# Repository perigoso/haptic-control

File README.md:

# haptic-control

PCB designed for (Someone else's) masters degree final project in eletrical-engineering

Made in the context of a research internship at IPL (Polytechnic Institute of Leiria)

## Authors

- Rafael Silva
- João Silva

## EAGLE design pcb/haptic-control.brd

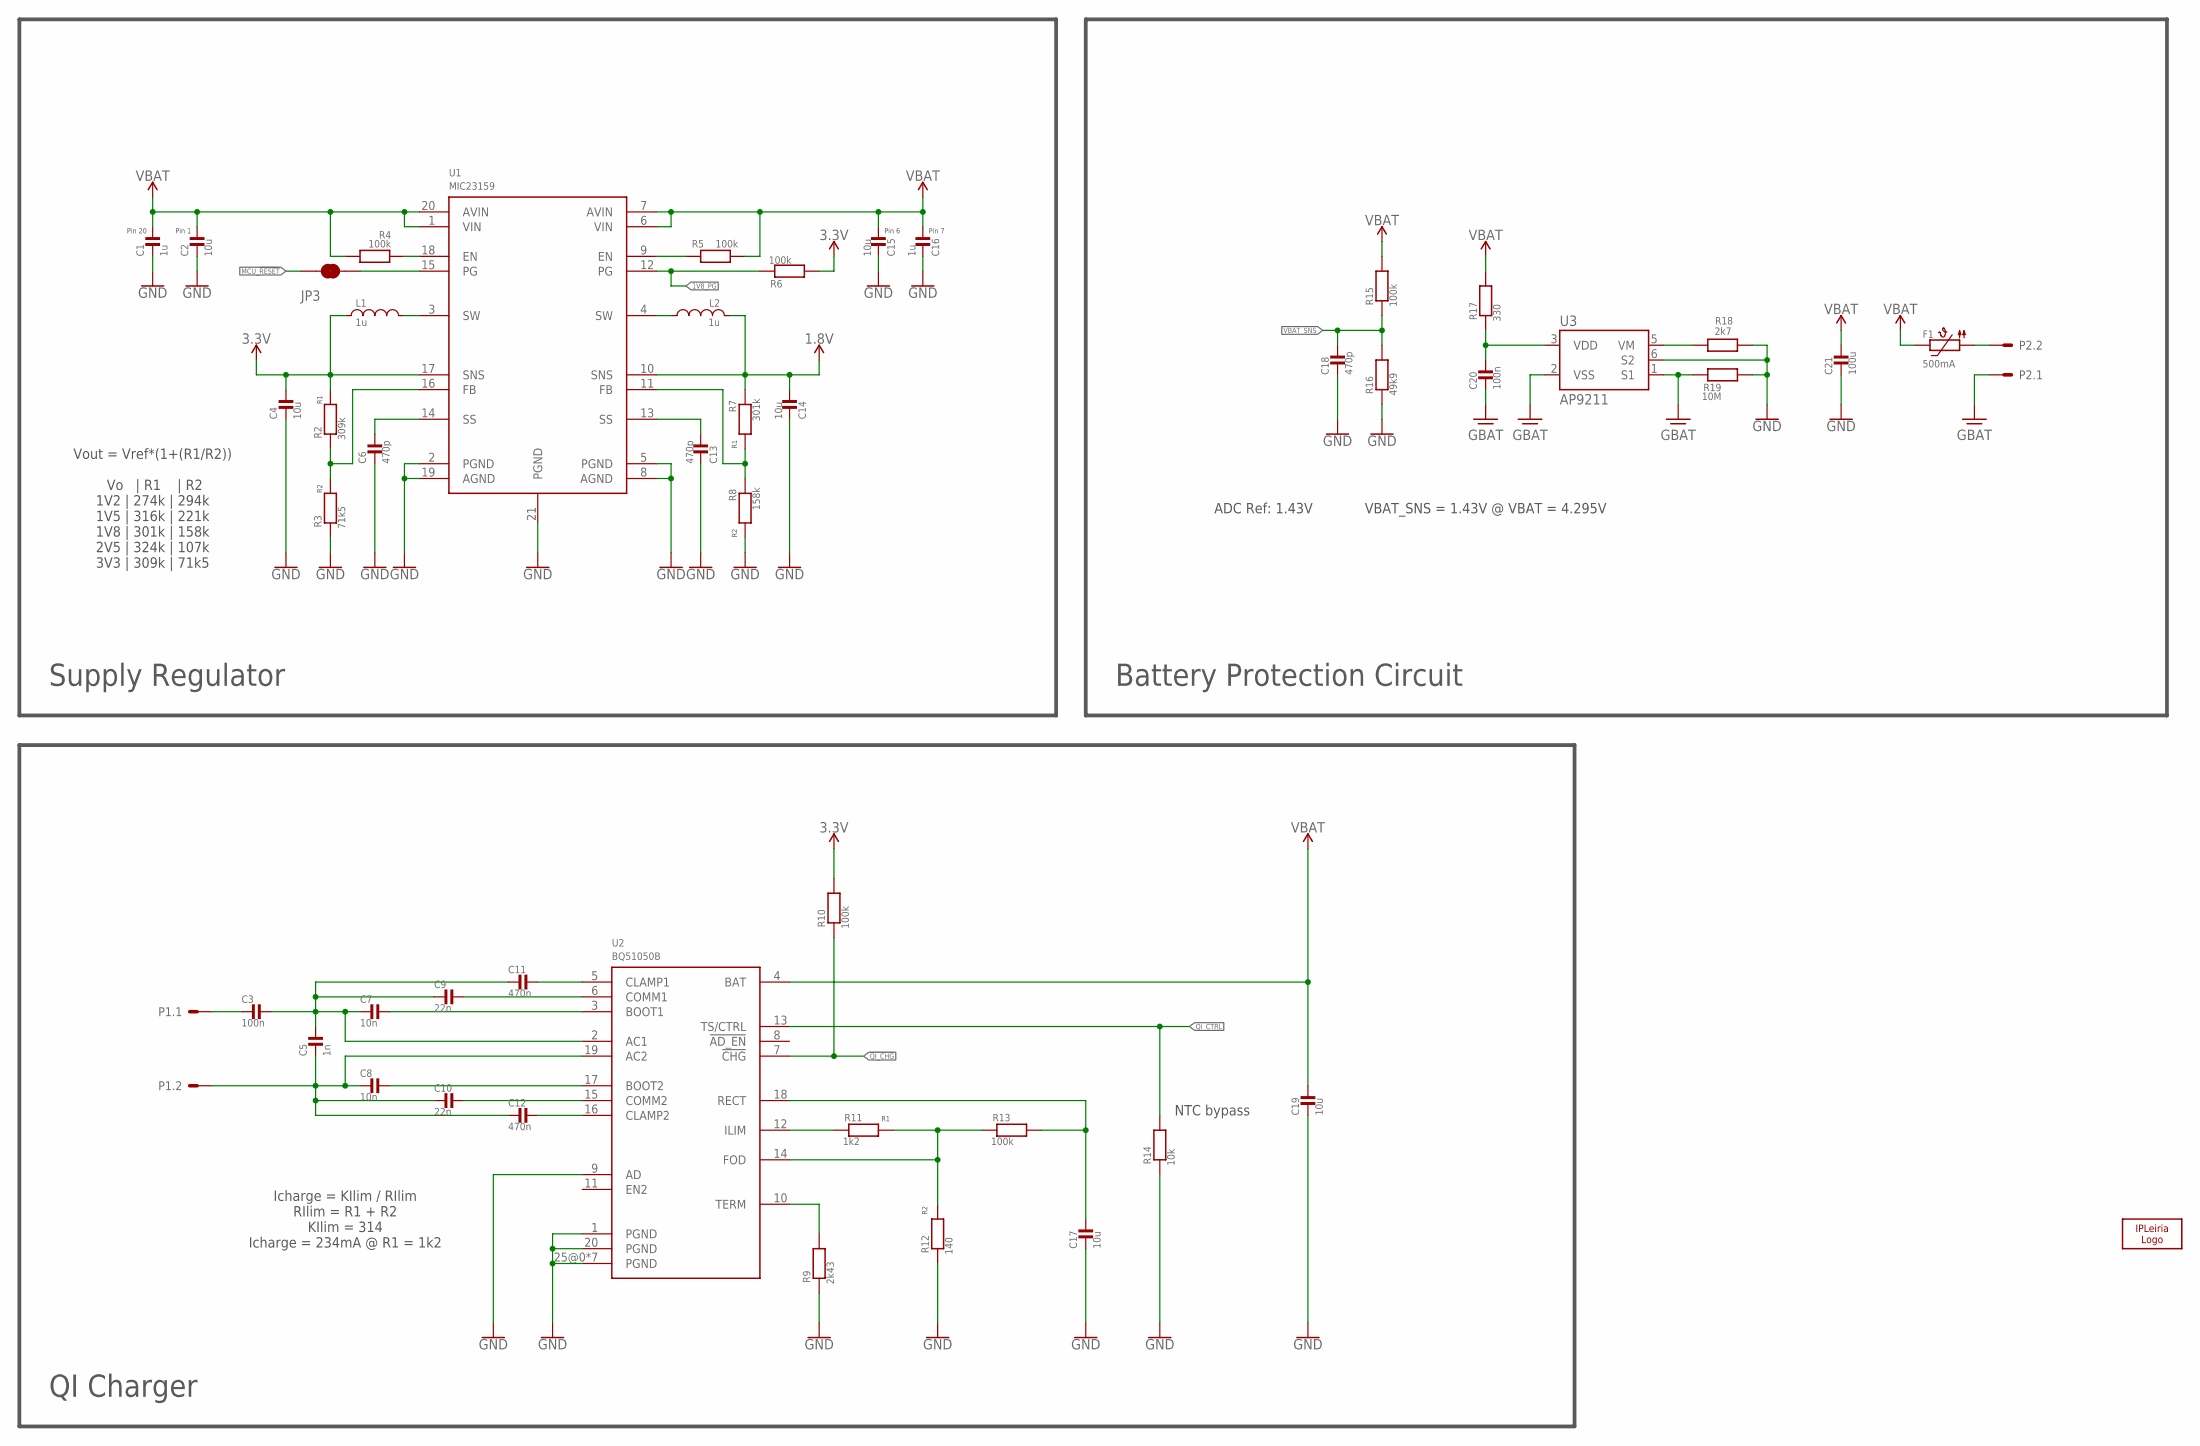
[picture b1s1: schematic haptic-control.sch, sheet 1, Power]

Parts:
C1, C16: 1u; 0603_WAVE
C2, C4, C14, C15, C17, C19: 10u; 0603_WAVE
C3, C20: 100n; _0402
C5: 1n; _0402
C6, C13, C18: 470p; _0402
C7, C8: 10n; _0402
C9, C10: 22n; _0402
C11, C12: 470n; _0402
C21: 100u; _1206
F1: 500mA; 0805
JP3: JUMPER-SMT_2_NC_TRACE_SILK; SMT-JUMPER_2_NC_TRACE_SILK
L1, L2: 1u; _0806
LOGO1: IPL-10MM; IPL_10MM
P1, P2: 2P-PAD_1X3.5; PAD1X3_5MM-2P
R2: 309k; _0402
R3: 71k5; _0402
R4, R5, R6, R10, R13, R15: 100k; _0402
R7: 301k; _0402
R8: 158k; _0402
R9: 2k43; _0402
R11: 1k2; _0402
R12: 140; _0402
R14: 10k; _0402
R16: 49k9; _0402
R17: 330; _0402
R18: 2k7; _0402
R19: 10M; _0402
U1: MIC23159; VQFN20
U2: BQ51050B; VQFN20
U3: AP9211; DFN2030-6

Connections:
1.8V: C14.P$1, L2.1, R7.1, U1.10 (SNS); also elsewhere on the board
1V8_PG: R6.1, U1.12 (PG); also elsewhere on the board
3.3V: C4.P$1, L1.1, R2.2, R6.2, R10.2, U1.17 (SNS); also elsewhere on the board
!QI_CHG: R10.1, U2.7 (!CHG); also elsewhere on the board
GBAT: C20.2, P2.1, R19.1, U3.1 (S1), U3.2 (VSS)
GND: C1.P$2, C2.P$2, C4.P$2, C6.2, C13.2, C14.P$2, C15.P$2, C16.P$2, C17.P$2, C18.2, C19.P$2, C21.2, R3.1, R8.2, R9.1, R12.1, R14.1, R16.1, R18.1, R19.2, U1.2 (PGND), U1.5 (PGND), U1.8 (AGND), U1.19 (AGND), U1.21 (PGND), U2.1 (PGND), U2.9 (AD), U2.20 (PGND), U2.25@0 (PGND), U2.25@1 (PGND), U2.25@2 (PGND), U2.25@3 (PGND), U2.25@4 (PGND), U2.25@5 (PGND), U2.25@6 (PGND), U3.6 (S2); also elsewhere on the board
MCU_!RESET: JP3.1; also elsewhere on the board
MPU_PWR: R5.1, U1.9 (EN)
unnamed: R18.2, U3.5 (VM)
unnamed: F1.1, P2.2
unnamed: C20.1, R17.1, U3.3 (VDD)
unnamed: R2.1, R3.2, U1.16 (FB)
unnamed: R4.1, U1.18 (EN)
unnamed: L1.2, U1.3 (SW)
unnamed: C6.1, U1.14 (SS)
unnamed: L2.2, U1.4 (SW)
unnamed: C13.1, U1.13 (SS)
unnamed: R7.2, R8.1, U1.11 (FB)
unnamed: R11.2, R12.2, R13.1, U2.14 (FOD)
unnamed: R11.1, U2.12 (ILIM)
unnamed: C17.P$1, R13.2, U2.18 (RECT)
unnamed: R9.2, U2.10 (TERM)
unnamed: C11.1, U2.5 (CLAMP1)
unnamed: C9.1, U2.6 (COMM1)
unnamed: C7.1, U2.3 (BOOT1)
unnamed: C12.1, U2.16 (CLAMP2)
unnamed: C10.1, U2.15 (COMM2)
unnamed: C8.1, U2.17 (BOOT2)
unnamed: C5.2, C8.2, C10.2, C12.2, P1.2, U2.19 (AC2)
unnamed: C3.1, C5.1, C7.2, C9.2, C11.2, U2.2 (AC1)
unnamed: C3.2, P1.1
unnamed: JP3.2, U1.15 (PG)
QI_CTRL: R14.2, U2.13 (TS/CTRL); also elsewhere on the board
VBAT: C1.P$1, C2.P$1, C15.P$1, C16.P$1, C19.P$1, C21.1, F1.2, R4.2, R5.2, R15.2, R17.2, U1.1 (VIN), U1.6 (VIN), U1.7 (AVIN), U1.20 (AVIN), U2.4 (BAT); also elsewhere on the board
VBAT_SNS: C18.1, R15.1, R16.2; also elsewhere on the board

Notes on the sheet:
Pin 20
Pin 1
Pin 7
Pin 6
Vout = Vref*(1+(R1/R2)) Vo | R1 | R2 1V2 | 274k | 294k 1V5 | 316k | 221k 1V8 | 301k | 158k 2V5 | 324k | 107k 3V3 | 309k | 71k5
VBAT_SNS = 1.43V @ VBAT = 4.295V
ADC Ref: 1.43V
Icharge = KIlim / RIlim RIlim = R1 + R2 KIlim = 314 Icharge = 234mA @ R1 = 1k2
Battery Protection Circuit
Supply Regulator
QI Charger
NTC bypass

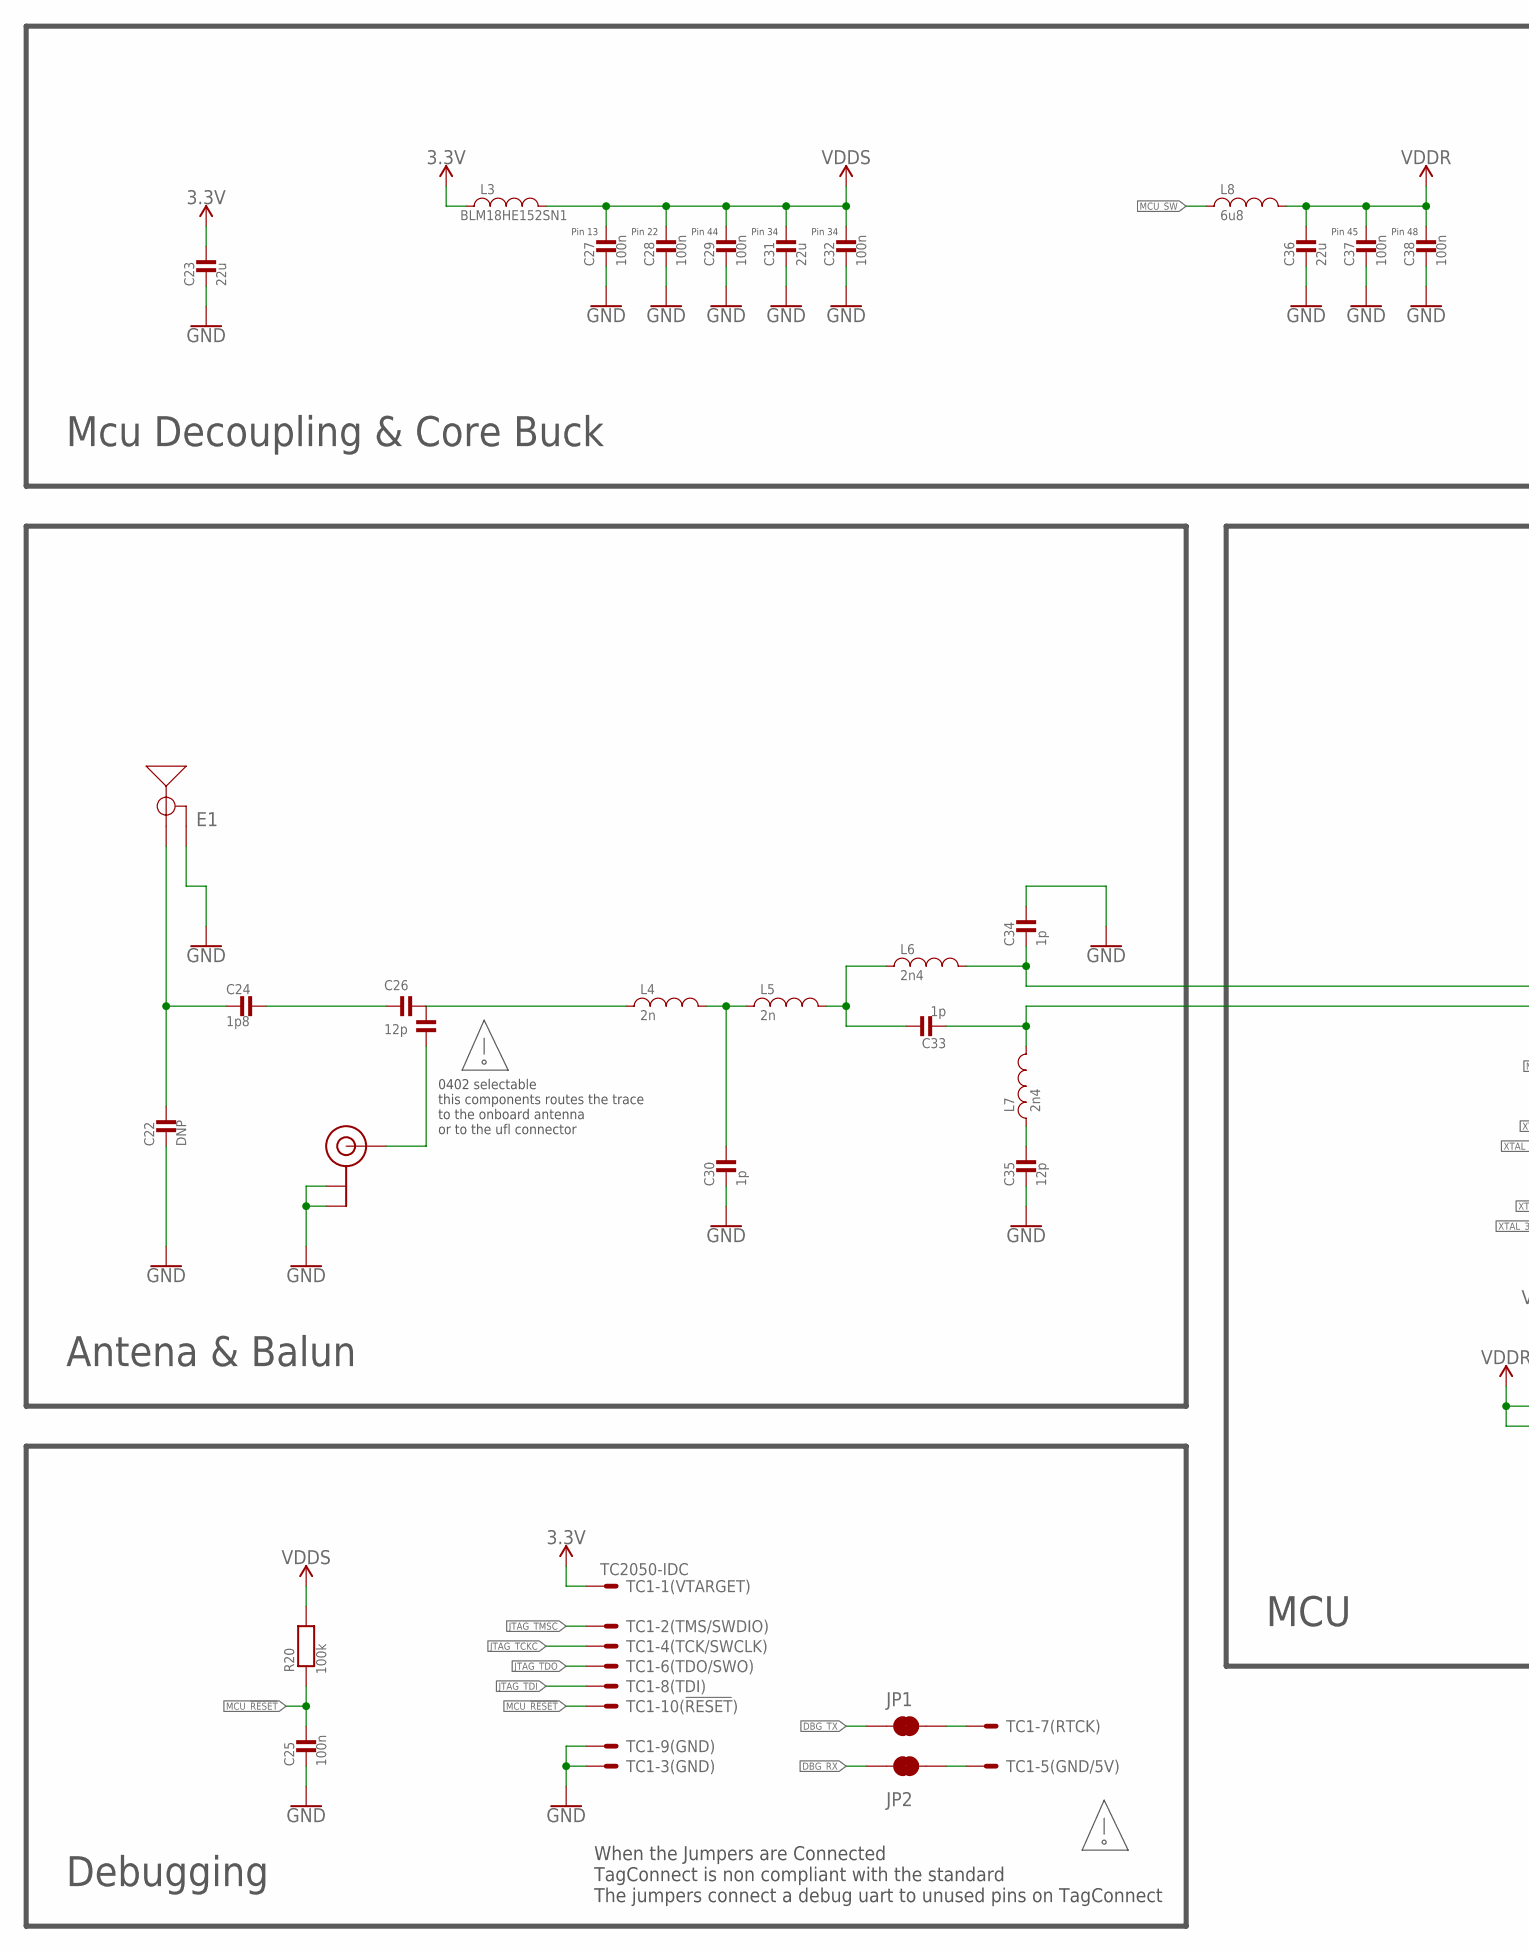
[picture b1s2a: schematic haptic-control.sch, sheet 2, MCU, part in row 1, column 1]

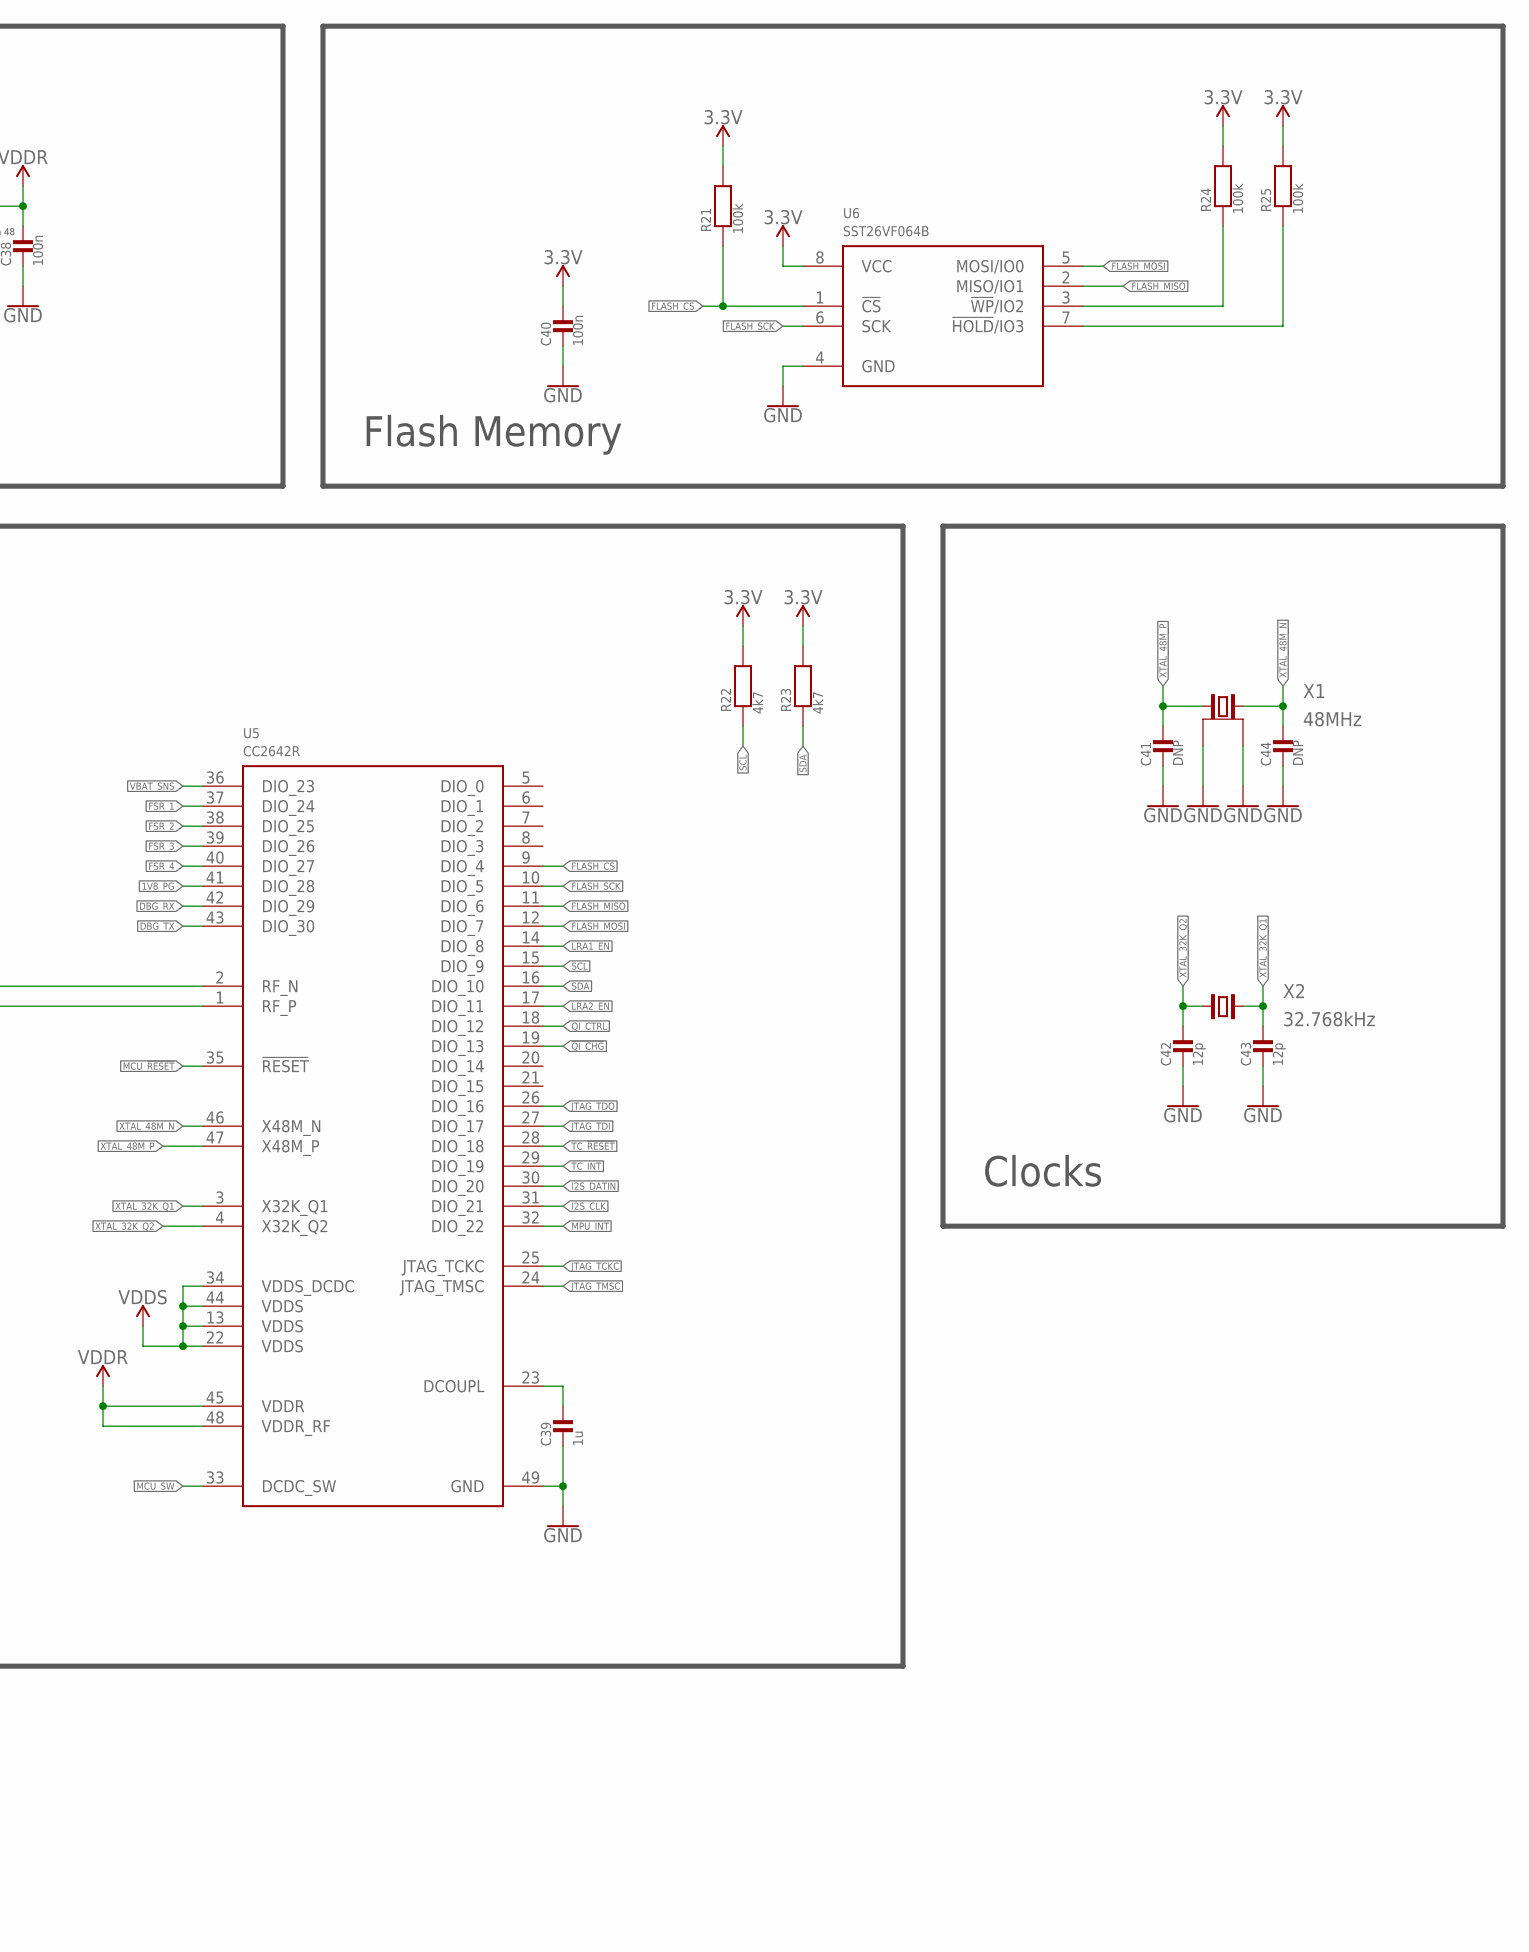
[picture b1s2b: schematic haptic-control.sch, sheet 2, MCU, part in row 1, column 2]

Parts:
A1: U.FL
C22, C41, C44: DNP; _0402
C23, C31, C36: 22u; 0603_WAVE
C24: 1p8; _0402
C25, C27, C28, C29, C32, C37, C38, C40: 100n; _0402
C26: 12p; _0402_SEL
C30, C33, C34: 1p; _0402
C35, C42, C43: 12p; _0402
C39: 1u; 0603_WAVE
E1: 2.4GHZTRACE-15.2MM; TRACE_ANTENNA_2.4GHZ_15.2MM
JP1, JP2: JUMPER-SMT_2_NC_TRACE_SILK; SMT-JUMPER_2_NC_TRACE_SILK
L3: BLM18HE152SN1; _0603
L4, L5: 2n; _0402
L6, L7: 2n4; _0402
L8: 6u8; _0806
R20, R21, R24, R25: 100k; _0402
R22, R23: 4k7; _0402
TC1: TC2050-IDC
U5: CC2642R; QFN48
U6: SST26VF064B; WSOIC8
X1: 48MHz; 4-SMD-3225
X2: 32.768kHz; 2-SMD-3215

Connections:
1V8_PG: U5.41 (DIO_28); also elsewhere on the board
3.3V: C23.P$1, C40.1, L3.1, R21.2, R22.2, R23.2, R24.2, R25.2, TC1.1, U6.8 (VCC); also elsewhere on the board
!QI_CHG: U5.19 (DIO_13); also elsewhere on the board
DBG_RX: JP2.1, U5.42 (DIO_29)
DBG_TX: JP1.1, U5.43 (DIO_30)
FLASH_CS: R21.1, U5.9 (DIO_4), U6.1 (!CS!)
FLASH_MISO: U5.11 (DIO_6), U6.2 (MISO/IO1)
FLASH_MOSI: U5.12 (DIO_7), U6.5 (MOSI/IO0)
FLASH_SCK: U5.10 (DIO_5), U6.6 (SCK)
FSR_1: U5.37 (DIO_24); also elsewhere on the board
FSR_2: U5.38 (DIO_25); also elsewhere on the board
FSR_3: U5.39 (DIO_26); also elsewhere on the board
FSR_4: U5.40 (DIO_27); also elsewhere on the board
GND: A1.P$1 (GND), A1.P$2 (GND), C22.2, C23.P$2, C25.2, C27.2, C28.2, C29.2, C30.2, C31.P$2, C32.2, C34.1, C35.2, C36.P$2, C37.2, C38.2, C39.P$2, C40.2, C41.2, C42.2, C43.2, C44.2, E1.GND, TC1.3, TC1.9, U5.49 (GND), U6.4 (GND), X1.2 (GND), X1.4 (GND); also elsewhere on the board
I2S_CLK: U5.31 (DIO_21); also elsewhere on the board
I2S_DATIN: U5.30 (DIO_20); also elsewhere on the board
JTAG_TCKC: TC1.4, U5.25 (JTAG_TCKC)
JTAG_TDI: TC1.8, U5.27 (DIO_17)
JTAG_TDO: TC1.6, U5.26 (DIO_16)
JTAG_TMSC: TC1.2, U5.24 (JTAG_TMSC)
LRA1_EN: U5.14 (DIO_8); also elsewhere on the board
LRA2_EN: U5.17 (DIO_11); also elsewhere on the board
MCU_!RESET: C25.1, R20.1, TC1.10, U5.35 (!RESET); also elsewhere on the board
MCU_SW: L8.1, U5.33 (DCDC_SW)
MPU_INT: U5.32 (DIO_22); also elsewhere on the board
unnamed: C34.2, L6.2, U5.2 (RF_N)
unnamed: C39.P$1, U5.23 (DCOUPL)
unnamed: C33.2, L7.2, U5.1 (RF_P)
unnamed: R24.1, U6.3 (!WP!/IO2)
unnamed: R25.1, U6.7 (!HOLD!/IO3)
unnamed: C26.1 (I), L4.1
unnamed: C24.1, C26.3 (O2)
unnamed: C35.1, L7.1
unnamed: C33.1, L5.2, L6.1
unnamed: C30.1, L4.2, L5.1
unnamed: C22.1, C24.2, E1.ANT (SIGNAL)
unnamed: A1.P$3 (SIGNAL), C26.2 (O1)
unnamed: JP2.2, TC1.5
unnamed: JP1.2, TC1.7
QI_CTRL: U5.18 (DIO_12); also elsewhere on the board
SCL: R22.1, U5.15 (DIO_9); also elsewhere on the board
SDA: R23.1, U5.16 (DIO_10); also elsewhere on the board
TC_!RESET: U5.28 (DIO_18); also elsewhere on the board
TC_INT: U5.29 (DIO_19); also elsewhere on the board
VBAT_SNS: U5.36 (DIO_23); also elsewhere on the board
VDDR: C36.P$1, C37.1, C38.1, L8.2, U5.45 (VDDR), U5.48 (VDDR_RF)
VDDS: C27.1, C28.1, C29.1, C31.P$1, C32.1, L3.2, R20.2, U5.13 (VDDS), U5.22 (VDDS), U5.34 (VDDS_DCDC), U5.44 (VDDS)
XTAL_32K_Q1: C43.1, U5.3 (X32K_Q1), X2.2
XTAL_32K_Q2: C42.1, U5.4 (X32K_Q2), X2.1
XTAL_48M_N: C44.1, U5.46 (X48M_N), X1.3 (2)
XTAL_48M_P: C41.1, U5.47 (X48M_P), X1.1

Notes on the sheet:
Pin 13
Pin 22
Pin 44
Pin 34
Pin 45
Pin 48
0402 selectable this components routes the trace to the onboard antenna or to the ufl connector
Mcu Decoupling & Core Buck
Flash Memory
MCU
Clocks
Antena & Balun
Debugging
When the Jumpers are Connected TagConnect is non compliant with the standard The jumpers connect a debug uart to unused pins on TagConnect

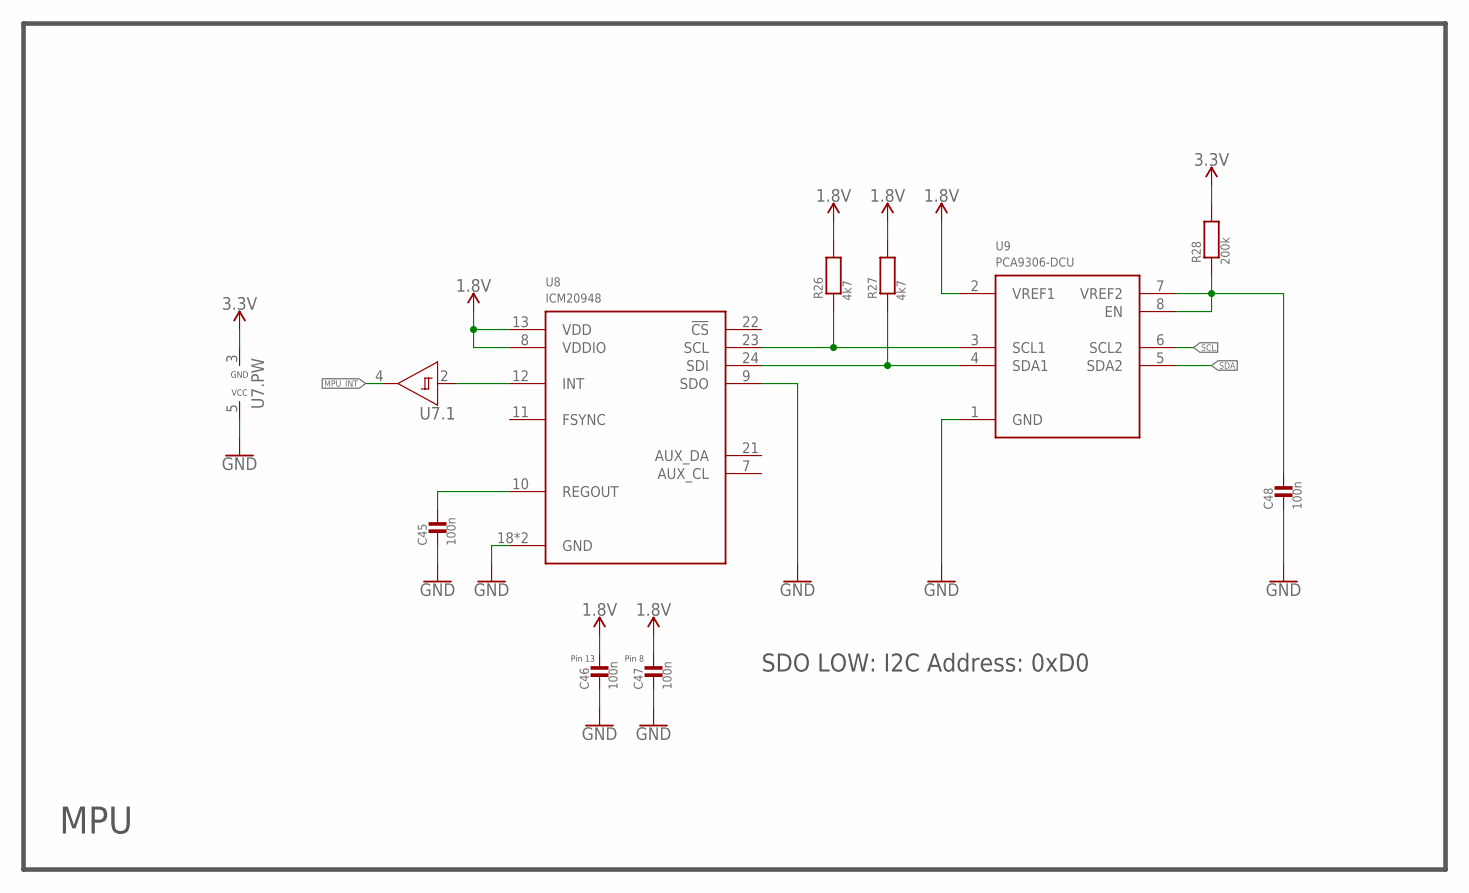
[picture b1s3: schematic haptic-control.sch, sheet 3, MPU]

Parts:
C45, C46, C47, C48: 100n; _0402
R26, R27: 4k7; _0402
R28: 200k; _0402
U7: 74LVC1G17; SC70-5
U8: ICM20948; QFN20
U9: PCA9306-DCU; VSSOP8

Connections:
1.8V: C46.1, C47.1, R26.2, R27.2, U8.8 (VDDIO), U8.13 (VDD), U9.2 (VREF1); also elsewhere on the board
3.3V: R28.2, U7.3 (GND); also elsewhere on the board
GND: C45.2, C46.2, C47.2, C48.2, U7.5 (VCC), U8.9 (SDO), U8.18 (GND), U8.20 (GND), U9.1 (GND); also elsewhere on the board
MPU_INT: U7.4 (Y); also elsewhere on the board
unnamed: U7.2 (A), U8.12 (INT)
unnamed: R26.1, U8.23 (SCL), U9.3 (SCL1)
unnamed: R27.1, U8.24 (SDI), U9.4 (SDA1)
unnamed: C45.1, U8.10 (REGOUT)
unnamed: C48.1, R28.1, U9.7 (VREF2), U9.8 (EN)
SCL: U9.6 (SCL2); also elsewhere on the board
SDA: U9.5 (SDA2); also elsewhere on the board

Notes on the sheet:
SDO LOW: I2C Address: 0xD0
Pin 13
Pin 8
MPU

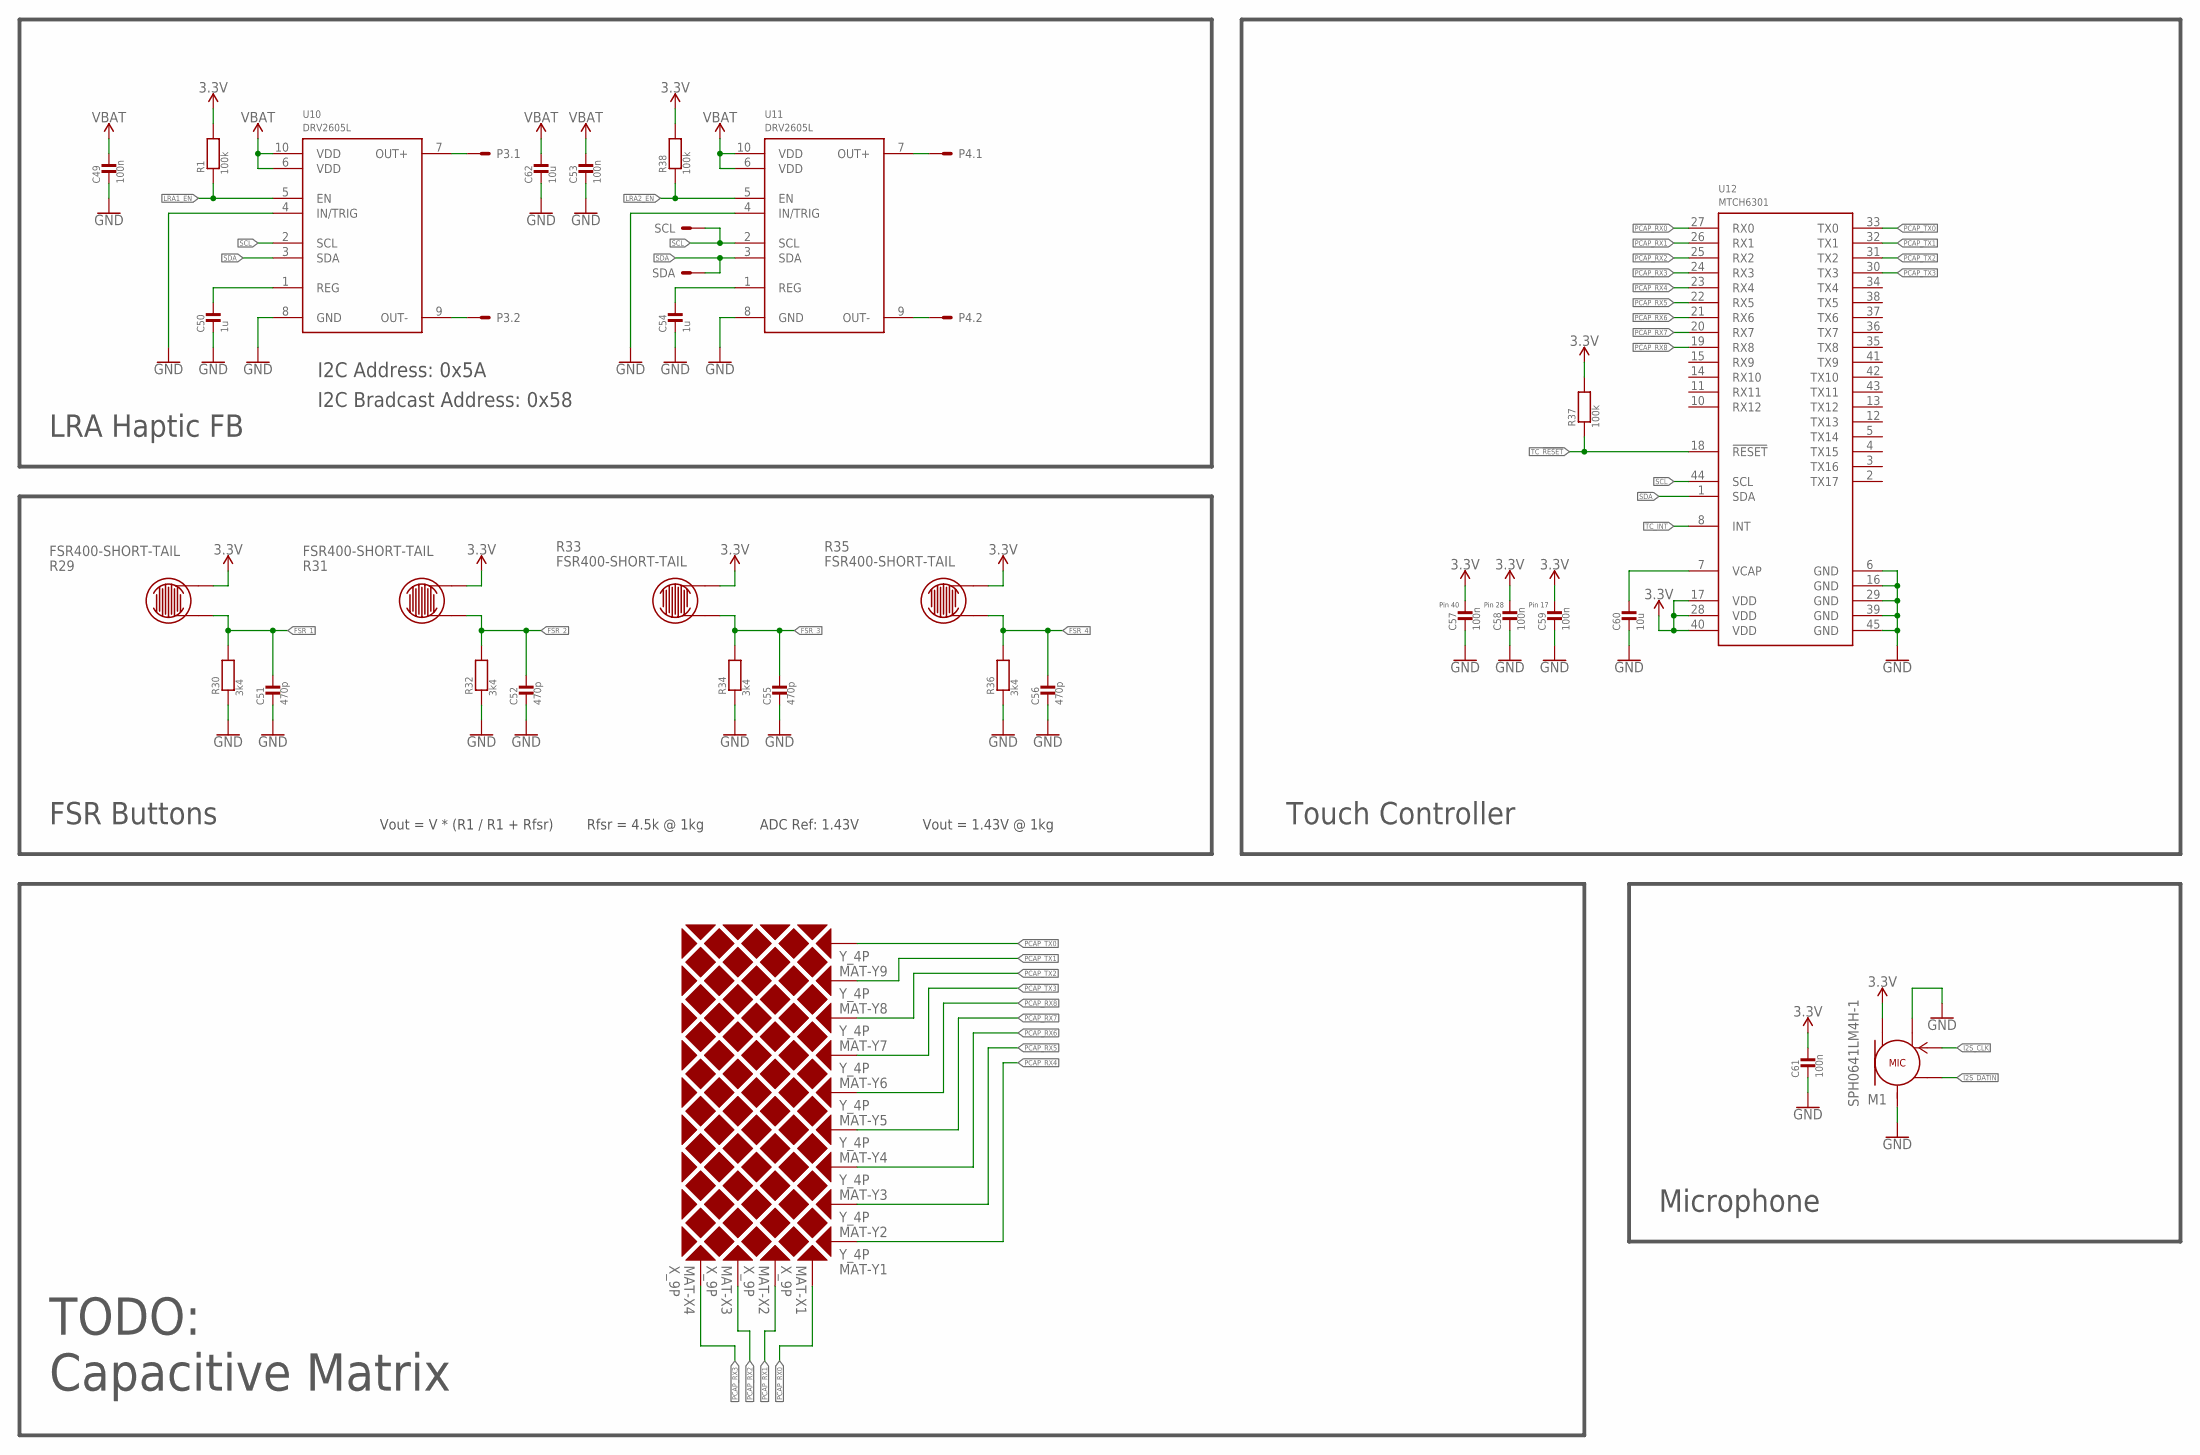
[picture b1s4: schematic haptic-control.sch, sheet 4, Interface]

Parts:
C49, C53, C57, C58, C59, C61: 100n; _0402
C50, C54: 1u; 0603_WAVE
C51, C52, C55, C56: 470p; _0402
C60, C62: 10u; 0603_WAVE
M1: SPH0641LM4H-1
MAT-X1, MAT-X2, MAT-X3, MAT-X4: X_9P; TOUCH_X_9P
MAT-Y1, MAT-Y2, MAT-Y3, MAT-Y4, MAT-Y5, MAT-Y6, MAT-Y7, MAT-Y8, MAT-Y9: Y_4P; TOUCH_Y_4P
P3, P4: 2P-PAD_1X3.5; PAD1X3_5MM-2P
R1, R37, R38: 100k; _0402
R29, R31, R33, R35: FSR400-SHORT-TAIL
R30, R32, R34, R36: 3k4; _0402
SCL: TEST_POINT
SDA: TEST_POINT
U10, U11: DRV2605L; VSSOP10
U12: MTCH6301; QFN44

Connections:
3.3V: C57.1, C58.1, C59.1, C61.1, M1.5 (VCC), R1.2, R29.2, R31.2, R33.1, R35.1, R37.2, R38.2, U12.17 (VDD), U12.28 (VDD), U12.40 (VDD); also elsewhere on the board
FSR_1: C51.1, R29.1, R30.2; also elsewhere on the board
FSR_2: C52.1, R31.1, R32.2; also elsewhere on the board
FSR_3: C55.1, R33.2, R34.2; also elsewhere on the board
FSR_4: C56.1, R35.2, R36.2; also elsewhere on the board
GND: C49.2, C50.P$2, C51.2, C52.2, C53.2, C54.P$2, C55.2, C56.2, C57.2, C58.2, C59.2, C60.P$2, C61.2, C62.P$2, M1.2 (SEL), M1.3 (GND), R30.1, R32.1, R34.1, R36.1, U10.4 (IN/TRIG), U10.8 (GND), U11.4 (IN/TRIG), U11.8 (GND), U12.6 (GND), U12.16 (GND), U12.29 (GND), U12.39 (GND), U12.45 (GND); also elsewhere on the board
I2S_CLK: M1.4 (CLK); also elsewhere on the board
I2S_DATIN: M1.1 (DAT); also elsewhere on the board
LRA1_EN: R1.1, U10.5 (EN); also elsewhere on the board
LRA2_EN: R38.1, U11.5 (EN); also elsewhere on the board
unnamed: C60.P$1, U12.7 (VCAP)
unnamed: P3.1, U10.7 (OUT+)
unnamed: P3.2, U10.9 (OUT-)
unnamed: P4.1, U11.7 (OUT+)
unnamed: P4.2, U11.9 (OUT-)
unnamed: C50.P$1, U10.1 (REG)
unnamed: C54.P$1, U11.1 (REG)
PCAP_RX0: MAT-X1.P$2, U12.27 (RX0)
PCAP_RX1: MAT-X2.P$2, U12.26 (RX1)
PCAP_RX2: MAT-X3.P$2, U12.25 (RX2)
PCAP_RX3: MAT-X4.P$2, U12.24 (RX3)
PCAP_RX4: MAT-Y1.P$2, MAT-Y1.P$3, MAT-Y1.P$4, MAT-Y1.P$5, MAT-Y1.P$8, U12.23 (RX4)
PCAP_RX5: MAT-Y2.P$2, MAT-Y2.P$3, MAT-Y2.P$4, MAT-Y2.P$5, MAT-Y2.P$8, U12.22 (RX5)
PCAP_RX6: MAT-Y3.P$2, MAT-Y3.P$3, MAT-Y3.P$4, MAT-Y3.P$5, MAT-Y3.P$8, U12.21 (RX6)
PCAP_RX7: MAT-Y4.P$2, MAT-Y4.P$3, MAT-Y4.P$4, MAT-Y4.P$5, MAT-Y4.P$8, U12.20 (RX7)
PCAP_RX8: MAT-Y5.P$2, MAT-Y5.P$3, MAT-Y5.P$4, MAT-Y5.P$5, MAT-Y5.P$8, U12.19 (RX8)
PCAP_TX0: MAT-Y9.P$2, MAT-Y9.P$3, MAT-Y9.P$4, MAT-Y9.P$5, MAT-Y9.P$8, U12.33 (TX0)
PCAP_TX1: MAT-Y8.P$2, MAT-Y8.P$3, MAT-Y8.P$4, MAT-Y8.P$5, MAT-Y8.P$8, U12.32 (TX1)
PCAP_TX2: MAT-Y7.P$2, MAT-Y7.P$3, MAT-Y7.P$4, MAT-Y7.P$5, MAT-Y7.P$8, U12.31 (TX2)
PCAP_TX3: MAT-Y6.P$2, MAT-Y6.P$3, MAT-Y6.P$4, MAT-Y6.P$5, MAT-Y6.P$8, U12.30 (TX3)
SCL: SCL.1, U10.2 (SCL), U11.2 (SCL), U12.44 (SCL); also elsewhere on the board
SDA: SDA.1, U10.3 (SDA), U11.3 (SDA), U12.1 (SDA); also elsewhere on the board
TC_!RESET: R37.1, U12.18 (!RESET); also elsewhere on the board
TC_INT: U12.8 (INT); also elsewhere on the board
VBAT: C49.1, C53.1, C62.P$1, U10.6 (VDD), U10.10 (VDD), U11.6 (VDD), U11.10 (VDD); also elsewhere on the board

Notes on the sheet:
TODO: Capacitive Matrix
Pin 40
Pin 28
Pin 17
Vout = V * (R1 / R1 + Rfsr)
Rfsr = 4.5k @ 1kg
ADC Ref: 1.43V
Touch Controller
Microphone
FSR Buttons
LRA Haptic FB
Vout = 1.43V @ 1kg
I2C Bradcast Address: 0x58
I2C Address: 0x5A

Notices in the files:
pcb/haptic-control.sch:
LICENSE: Copyright © 2019 Tech4Home
